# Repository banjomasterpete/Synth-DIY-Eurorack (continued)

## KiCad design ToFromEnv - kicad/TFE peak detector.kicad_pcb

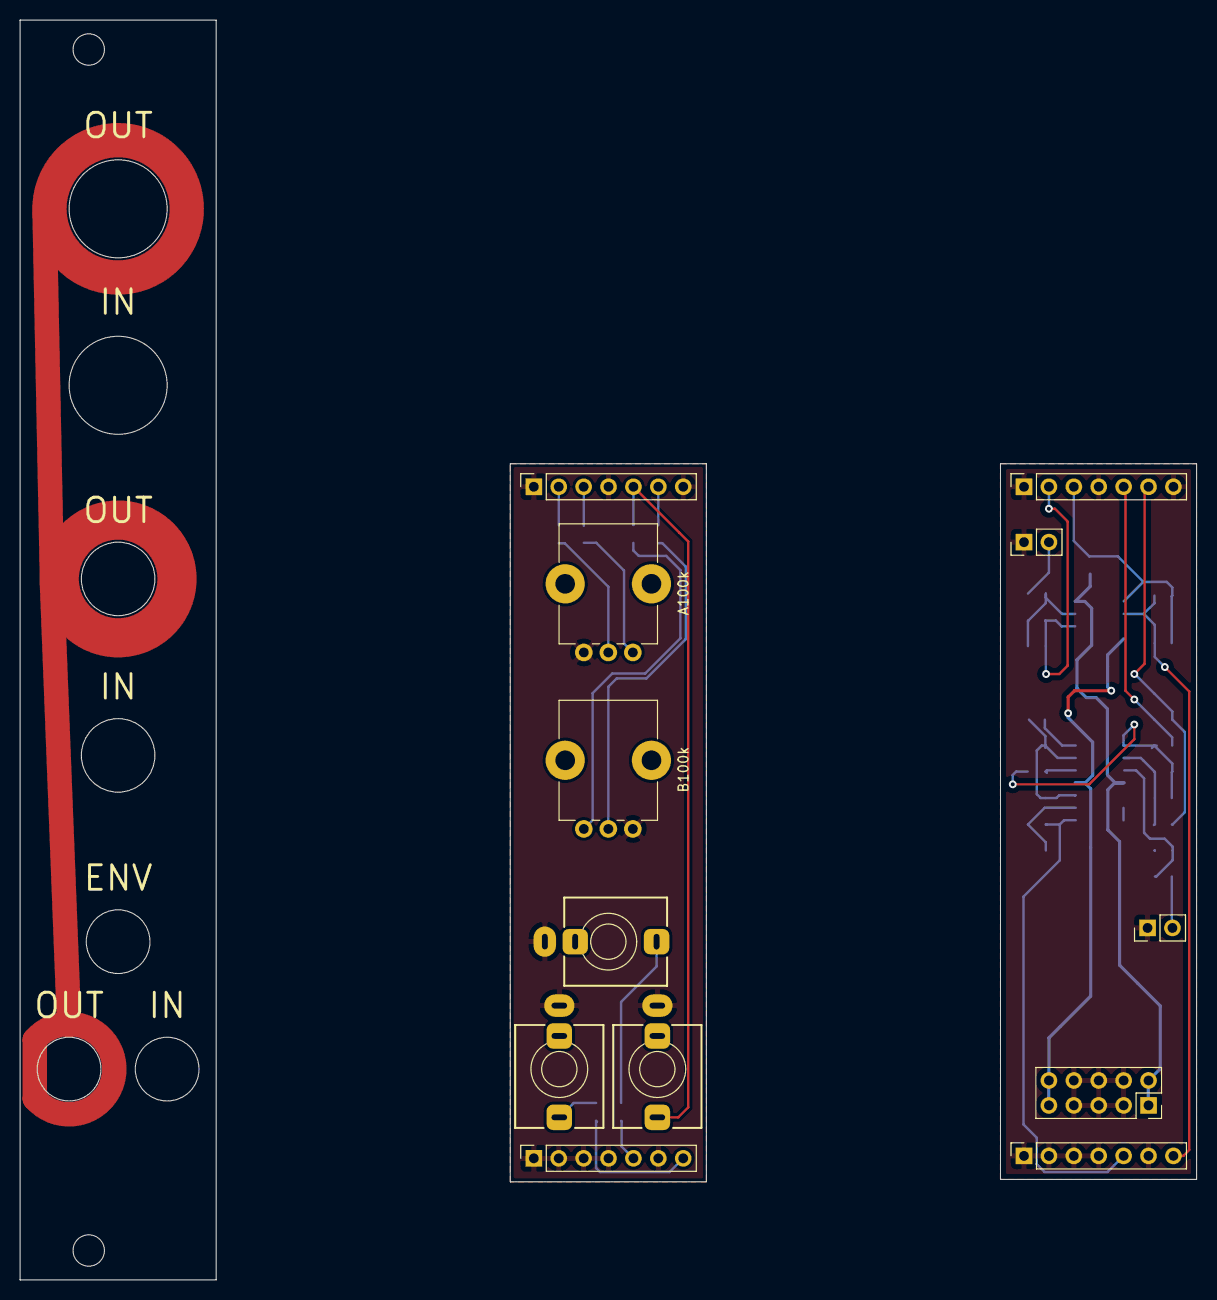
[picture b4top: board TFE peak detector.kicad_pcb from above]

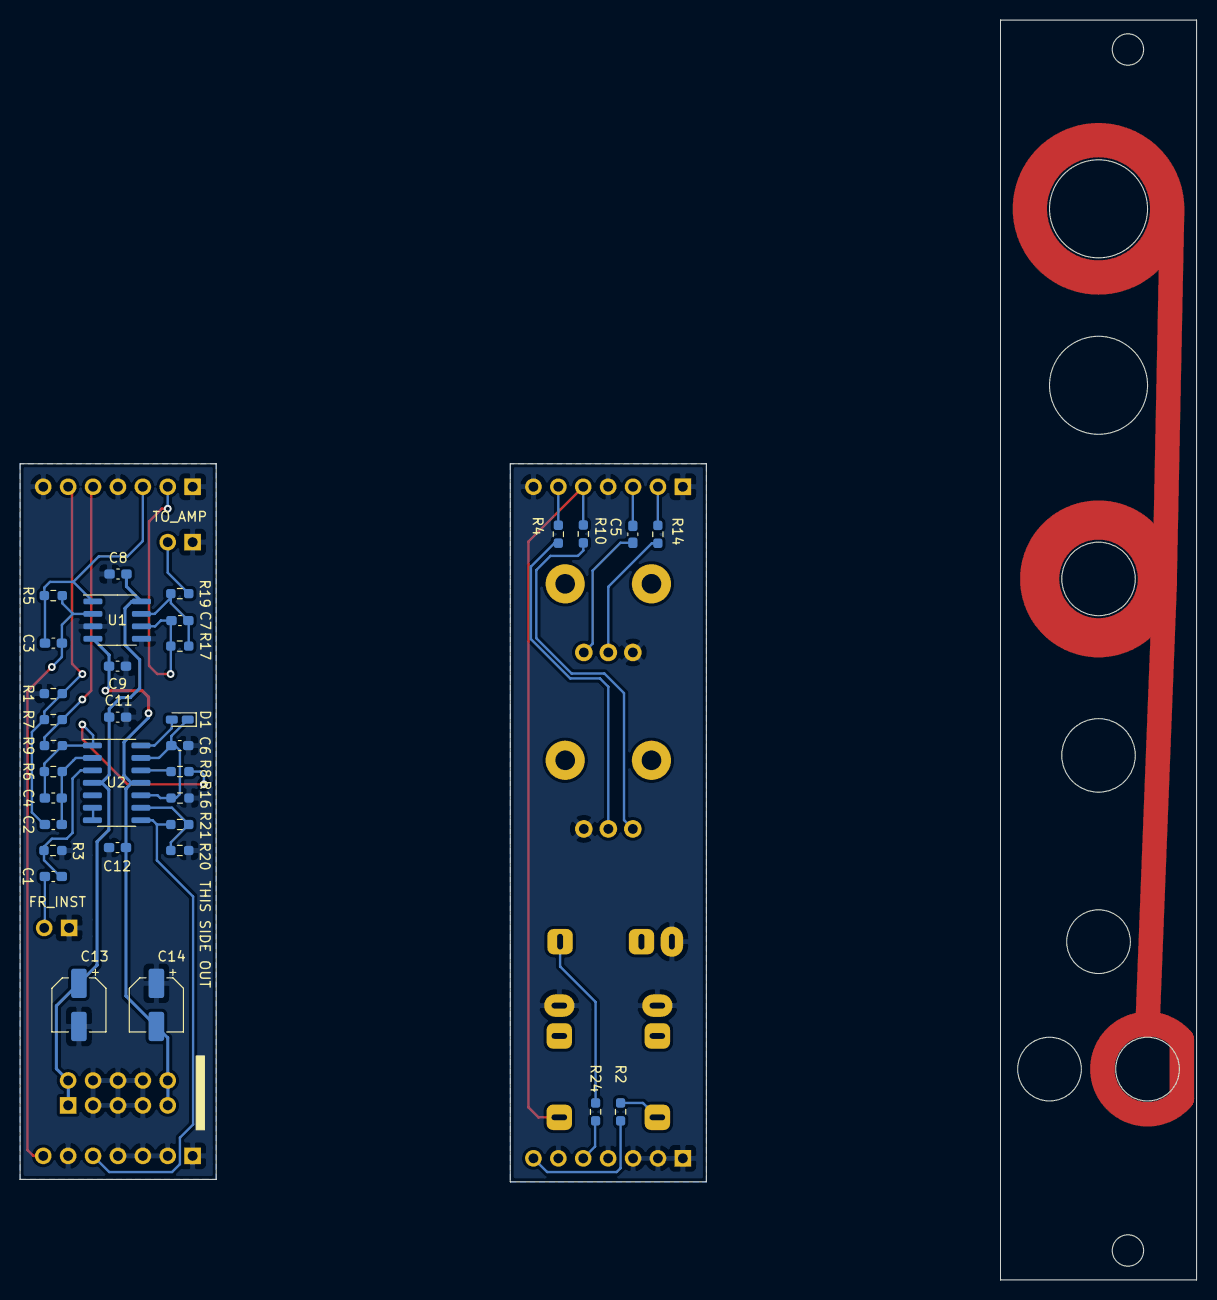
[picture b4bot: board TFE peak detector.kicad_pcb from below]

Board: 2 copper layers, 120.0 x 128.5 mm, 45 parts (33 on the bottom side), 33 nets.

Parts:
C1: 47n; C_0603_1608Metric_Pad1.08x0.95mm_HandSolder
C2: 4.7u; C_0603_1608Metric_Pad1.08x0.95mm_HandSolder
C3, C7: 10p; C_0603_1608Metric_Pad1.08x0.95mm_HandSolder
C4: 100p; C_0603_1608Metric_Pad1.08x0.95mm_HandSolder
C5, C6: 10u; C_0603_1608Metric_Pad1.08x0.95mm_HandSolder
C8, C9, C11, C12: 100n; C_0603_1608Metric_Pad1.08x0.95mm_HandSolder
C13, C14: 10u; CP_Elec_5x5.4
D1: D; D_0603_1608Metric_Castellated
J1: FR_INST; PinHeader_1x02_P2.54mm_Vertical
J2: FR_MOD; Jack_3.5mm_QingPu_WQP-PJ398SM_Vertical
J3: TO_MOD; Jack_3.5mm_QingPu_WQP-PJ398SM_Vertical
J4: TO_AMP; PinHeader_1x02_P2.54mm_Vertical
J5, J9: Conn_01x07_Female; PinSocket_1x07_P2.54mm_Vertical
J6, J10: Conn_01x07_Male; PinSocket_1x07_P2.54mm_Vertical
J7: ENV; Jack_3.5mm_QingPu_WQP-PJ398SM_Vertical
J8: Conn_02x05_Odd_Even; PinSocket_2x05_P2.54mm_Vertical
R1: 6k8; R_0603_1608Metric_Pad0.98x0.95mm_HandSolder
R2: 100k; R_0603_1608Metric_Pad0.98x0.95mm_HandSolder
R3, R6: 2M2; R_0603_1608Metric_Pad0.98x0.95mm_HandSolder
R4: 3k3; R_0603_1608Metric_Pad0.98x0.95mm_HandSolder
R5: 39k; R_0603_1608Metric_Pad0.98x0.95mm_HandSolder
R7: 62k; R_0603_1608Metric_Pad0.98x0.95mm_HandSolder
R8, R19, R24: 1k; R_0603_1608Metric_Pad0.98x0.95mm_HandSolder
R9: 470R; R_0603_1608Metric_Pad0.98x0.95mm_HandSolder
R10: 15k; R_0603_1608Metric_Pad0.98x0.95mm_HandSolder
R14, R16, R17: 10k; R_0603_1608Metric_Pad0.98x0.95mm_HandSolder
R20, R21: 470k; R_0603_1608Metric_Pad0.98x0.95mm_HandSolder
RV1: B100k; Potentiometer_Alps_RK09K_Single_Vertical
RV2: A100k; Potentiometer_Alps_RK09K_Single_Vertical
U1: TL072; SOIC-8_3.9x4.9mm_P1.27mm
U2: TL074; SOIC-14_3.9x8.7mm_P1.27mm

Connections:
+12V: C8.2, C11.2, C13.1, J8.1, J8.2, U1.8, U2.4
-12V: C9.1, C12.1, C14.2, J8.9, J8.10, U1.4, U2.11
ENV_B: J5.5, R21.1, U2.8
ENV_P: J6.5, R24.2
FR_MOD_B: C3.2, J5.7, R5.1, U1.2
FR_MOD_P: J6.7, R2.2
GND: C6.1, C8.1, C9.2, C11.1, C12.2, C13.2, C14.1, J1.1, J4.1, J5.1, J5.2, J5.3, J5.4, J5.6, J8.3, J8.4, J8.5, J8.6, J8.7, J8.8, J9.1, J9.4, J9.7, R1.2, R3.1, R16.2, R20.1, U1.3, U1.5
GND_P: J2.S, J3.S, J6.1, J6.2, J6.3, J6.4, J6.6, J7.S, J10.1, J10.4, J10.7, RV1.1, RV2.3
INST_AMP_2_B: C2.2, J9.6, R1.1, R7.2
INST_AMP_2_P: J10.6, R4.1
INST_AMP_3_B: J9.5, R7.1, R9.2
INST_AMT_3_P: J3.T, J10.5, R10.1
unnamed: C1.1, R3.2, U2.3
unnamed: C1.2, J1.2
unnamed: C2.1, C4.2, R6.1, U2.2
unnamed: C4.1, R6.2, R8.1, R9.1, U2.1
unnamed: C5.2, RV2.1
unnamed: C6.2, D1.1, R16.1, U2.10, U2.13
unnamed: C7.1, R17.2, R19.1, U1.7
unnamed: D1.2, U2.14
unnamed: J2.T, R2.1
unnamed: J4.2, R19.2
unnamed: J7.T, R24.1
unnamed: R4.2, RV1.2
unnamed: R8.2, U2.12
unnamed: R10.2, RV1.3
unnamed: R14.1, RV2.2
unnamed: R20.2, R21.2, U2.9
unnamed: U2.6, U2.7
OUT_AMP_1_B: C3.1, J9.3, R5.2, U1.1
OUT_AMP_1_P: C5.1, J10.3
OUT_AMP_2_B: C7.2, J9.2, R17.1, U1.6
OUT_AMP_2_P: J10.2, R14.2

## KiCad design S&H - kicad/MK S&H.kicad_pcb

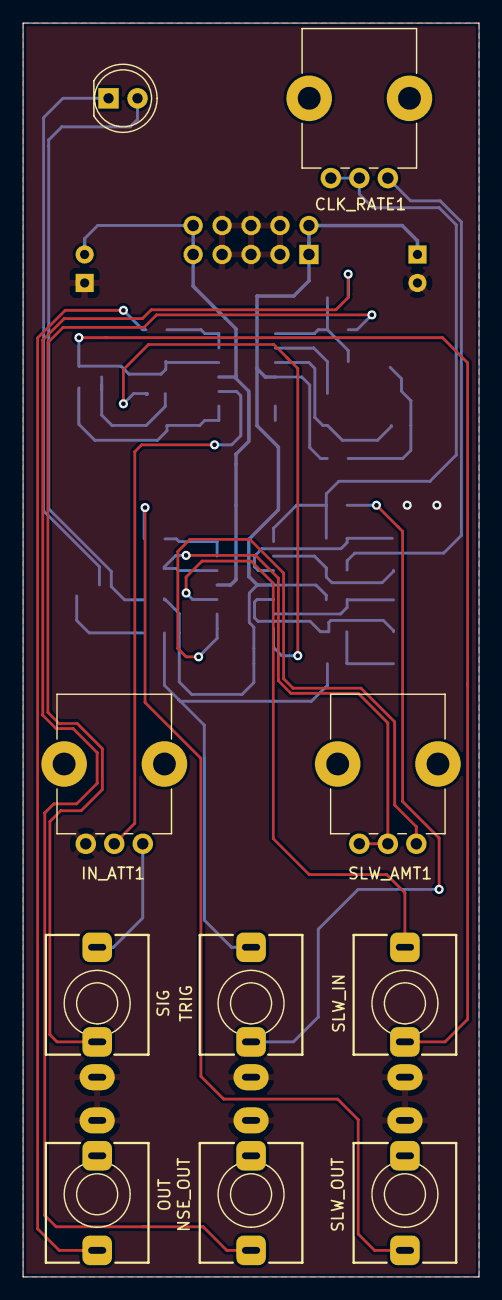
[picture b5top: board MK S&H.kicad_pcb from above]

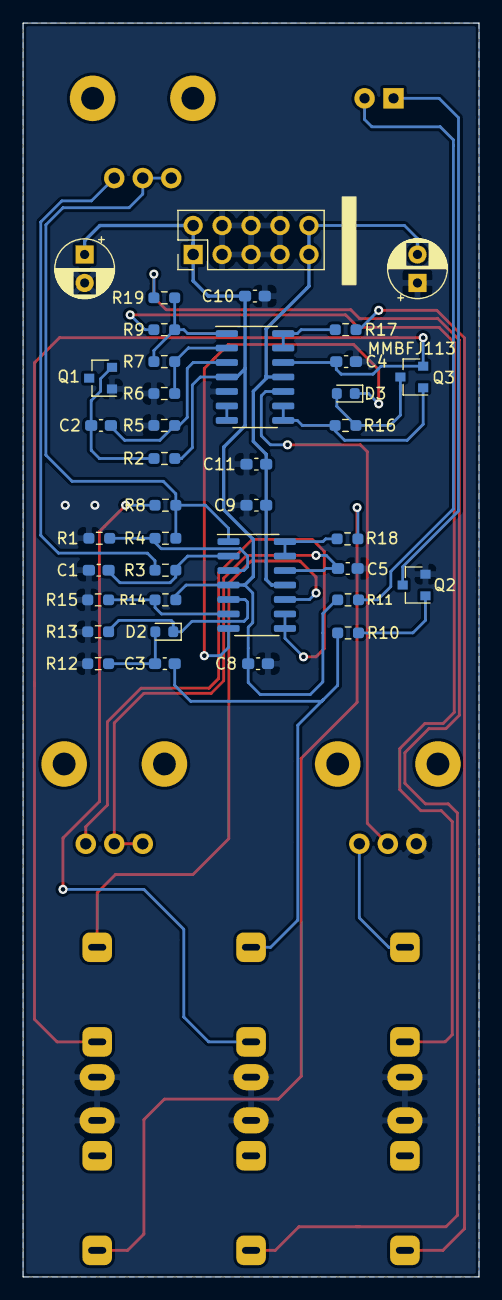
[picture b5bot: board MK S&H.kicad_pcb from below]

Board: 2 copper layers, 40.0 x 110.0 mm, 48 parts (38 on the bottom side), 35 nets.

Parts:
C1, C2: 1uF; C_0603_1608Metric_Pad1.08x0.95mm_HandSolder
C3: 1nF; C_0603_1608Metric_Pad1.08x0.95mm_HandSolder
C4, C8, C9, C10, C11: 100nF; C_0603_1608Metric_Pad1.08x0.95mm_HandSolder
C5: 470nF; C_0603_1608Metric_Pad1.08x0.95mm_HandSolder
C6, C7: CP; CP_Radial_D5.0mm_P2.50mm
CLK_RATE1: 250k; Potentiometer_Alps_RK09K_Single_Vertical
D1: LED; LED_D5.0mm
D2, D3: D; D_0603_1608Metric
IN_ATT1: 100k; Potentiometer_Alps_RK09K_Single_Vertical
J1: TRIG; Jack_3.5mm_QingPu_WQP-PJ398SM_Vertical
J2: SIG; Jack_3.5mm_QingPu_WQP-PJ398SM_Vertical
J3: SLW_IN; Jack_3.5mm_QingPu_WQP-PJ398SM_Vertical
J4: OUT; Jack_3.5mm_QingPu_WQP-PJ398SM_Vertical
J5: SLW_OUT; Jack_3.5mm_QingPu_WQP-PJ398SM_Vertical
J6: Conn_02x05_Odd_Even; PinHeader_2x05_P2.54mm_Vertical
J7: NSE_OUT; Jack_3.5mm_QingPu_WQP-PJ398SM_Vertical
Q1: BC847B; SOT-23
Q2: BC848; SOT-23
Q3: MMBFJ113; SOT-23
R1, R4, R5, R7, R8, R12, R13, R14: 100k; R_0603_1608Metric_Pad0.98x0.95mm_HandSolder
R2: 220k; R_0603_1608Metric_Pad0.98x0.95mm_HandSolder
R3: 2k; R_0603_1608Metric_Pad0.98x0.95mm_HandSolder
R6: 470R; R_0603_1608Metric_Pad0.98x0.95mm_HandSolder
R9, R11, R17, R18, R19: 1k; R_0603_1608Metric_Pad0.98x0.95mm_HandSolder
R10: 51k; R_0603_1608Metric_Pad0.98x0.95mm_HandSolder
R15: 33k; R_0603_1608Metric_Pad0.98x0.95mm_HandSolder
R16: 1M; R_0603_1608Metric_Pad0.98x0.95mm_HandSolder
SLW_AMT1: 100k; Potentiometer_Alps_RK09K_Single_Vertical
U1, U2: TL074; SOIC-14_3.9x8.7mm_P1.27mm

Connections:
+12V: C6.1, C8.1, C10.1, J6.1, J6.2, R2.1, R11.1, R14.2, U1.4, U2.4
-12V: C7.2, C9.2, C11.2, J6.9, J6.10, U1.11, U2.11
GND: C1.2, C4.2, C5.2, C6.2, C7.1, C8.2, C9.1, C10.2, C11.1, IN_ATT1.3, J1.S, J2.S, J3.S, J4.S, J5.S, J6.3, J6.4, J6.5, J6.6, J6.7, J6.8, J7.S, Q1.1, Q2.2, R1.2, R5.2, R6.2, R12.2, R13.2, R15.1, U2.5
NOISE: J2.TN, R9.1
unnamed: C1.1, R3.2, U1.2
unnamed: C2.1, R5.1, U2.3
unnamed: C2.2, Q1.2, R2.2
unnamed: C3.1, D2.2, R12.1
unnamed: C3.2, J1.T, R10.2
unnamed: C4.1, J3.TN, Q3.2, U2.12
unnamed: C5.1, SLW_AMT1.2, SLW_AMT1.3, U1.12
unnamed: CLK_RATE1.1, R3.1
unnamed: CLK_RATE1.2, CLK_RATE1.3, R4.1, R8.2, U1.1
unnamed: D1.1, Q2.3
unnamed: D1.2, R11.2
unnamed: D2.1, R13.1, U1.5
unnamed: D3.1, U1.7
unnamed: D3.2, Q3.3, R16.1
unnamed: IN_ATT1.1, J2.T
unnamed: IN_ATT1.2, U2.10
unnamed: J1.TN, R8.1
unnamed: J3.T, U1.10
unnamed: J4.T, R17.1
unnamed: J5.T, R18.1
unnamed: J7.T, R19.1
unnamed: Q2.1, R10.1
unnamed: Q3.1, R16.2, U2.8, U2.9
unnamed: R1.1, R4.2, U1.3
unnamed: R6.1, R7.1, U2.2
unnamed: R14.1, R15.2, U1.6
unnamed: R17.2, U2.13, U2.14
unnamed: R18.2, U1.13, U1.14
unnamed: R7.2, R9.2, R19.2, U2.1
unnamed: SLW_AMT1.1, U1.8, U1.9
unnamed: U2.6, U2.7

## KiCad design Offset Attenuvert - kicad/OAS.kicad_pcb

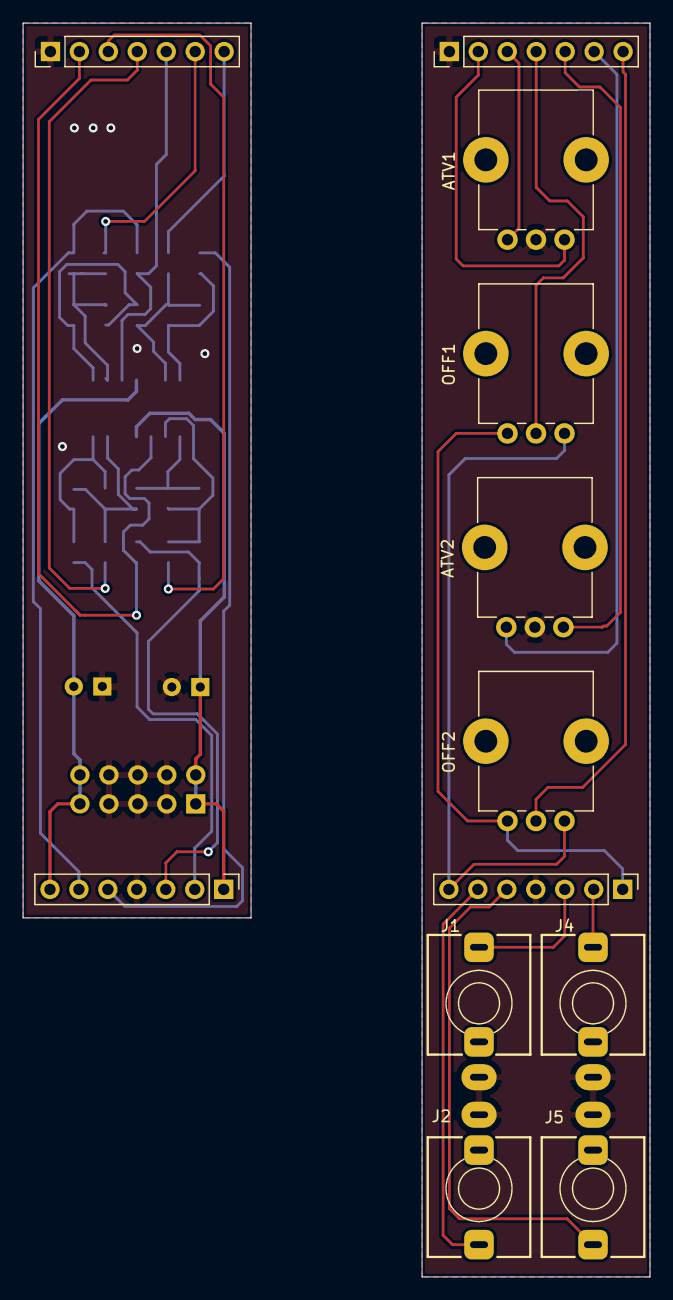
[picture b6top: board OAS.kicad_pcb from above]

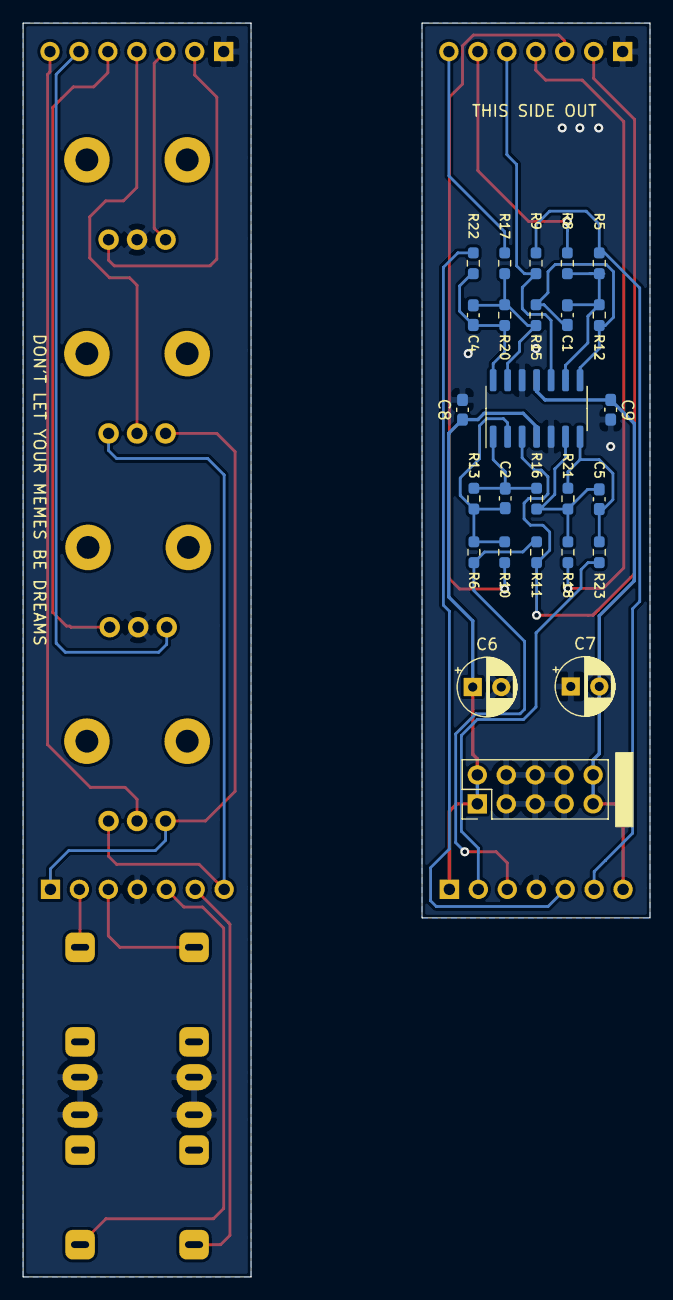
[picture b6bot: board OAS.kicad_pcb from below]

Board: 2 copper layers, 55.0 x 110.0 mm, 38 parts (26 on the bottom side), 34 nets.

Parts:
ATV1, ATV2: 100k; Potentiometer_Alps_RK09K_Single_Vertical
C1, C2, C4, C5: 10pF; C_0603_1608Metric_Pad1.08x0.95mm_HandSolder
C6, C7: 10uF; CP_Radial_D5.0mm_P2.50mm
C8, C9: 100n; C_0603_1608Metric_Pad1.08x0.95mm_HandSolder
J1: IN1; Jack_3.5mm_QingPu_WQP-PJ398SM_Vertical
J2: IN2; Jack_3.5mm_QingPu_WQP-PJ398SM_Vertical
J3, J6: Conn_01x07_Male; PinHeader_1x07_P2.54mm_Vertical
J4: OUT1; Jack_3.5mm_QingPu_WQP-PJ398SM_Vertical
J5: OUT2; Jack_3.5mm_QingPu_WQP-PJ398SM_Vertical
J7: PWR; PinHeader_2x05_P2.54mm_Vertical
J8, J9: Conn_01x07_Female; PinHeader_1x07_P2.54mm_Vertical
OFF1, OFF2: 100k; Potentiometer_Alps_RK09K_Single_Vertical
R5, R6, R9, R11, R12, R13: 100k; R_0603_1608Metric_Pad0.98x0.95mm_HandSolder
R8, R10: 47k; R_0603_1608Metric_Pad0.98x0.95mm_HandSolder
R15, R16, R17, R18, R20, R21: 10k; R_0603_1608Metric_Pad0.98x0.95mm_HandSolder
R22, R23: 1k; R_0603_1608Metric_Pad0.98x0.95mm_HandSolder
U1: TL074; SO-14_3.9x8.65mm_P1.27mm

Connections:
12V_B: C6.1, C8.1, J6.1, J7.1, J7.2, U1.4
12V_P: J9.1, OFF1.3, OFF2.3
-12V_B: C7.2, C9.2, J6.7, J7.9, J7.10, U1.11
-12V_P: J9.7, OFF1.1, OFF2.1
ATV1_1_B: J3.2, R11.2, U1.3
ATV1_1_P: ATV1.1, J8.2
ATV1_3_B: J3.3, R10.2
ATV1_3_P: ATV1.3, J8.3
ATV2_1_B: J3.5, R9.2, U1.10
ATV2_1_P: ATV2.1, J8.5
ATV2_3_B: J3.6, R8.2
ATV2_3_P: ATV2.3, J8.6
GND_B: C6.2, C7.1, C8.2, C9.1, J3.1, J6.4, J7.3, J7.4, J7.5, J7.6, J7.7, J7.8, U1.5, U1.12
GND_P: ATV1.2, ATV2.2, J1.S, J2.S, J4.S, J5.S, J8.1, J9.4
IN1_T_B: J6.3, R6.1, R11.1
IN1_T_P: J1.T, J9.3
IN2_T_B: J6.6, R5.1, R9.1
IN2_T_P: J2.T, J9.6
unnamed: C1.1, R12.2, R15.1, U1.8
unnamed: C1.2, R5.2, R8.1, R12.1, U1.9
unnamed: C2.1, R13.2, R16.1, U1.1
unnamed: C2.2, R6.2, R10.1, R13.1, U1.2
unnamed: C4.1, R20.2, R22.1, U1.14
unnamed: C4.2, R15.2, R17.2, R20.1, U1.13
unnamed: C5.1, R21.2, R23.1, U1.7
unnamed: C5.2, R16.2, R18.2, R21.1, U1.6
OFF1_2_B: J3.4, R18.1
OFF1_2_P: J8.4, OFF1.2
OFF2_2_B: J3.7, R17.1
OFF2_2_P: J8.7, OFF2.2
OUT1_T_B: J6.2, R23.2
OUT1_T_P: J4.T, J9.2
OUT2_T_B: J6.5, R22.2
OUT2_T_P: J5.T, J9.5

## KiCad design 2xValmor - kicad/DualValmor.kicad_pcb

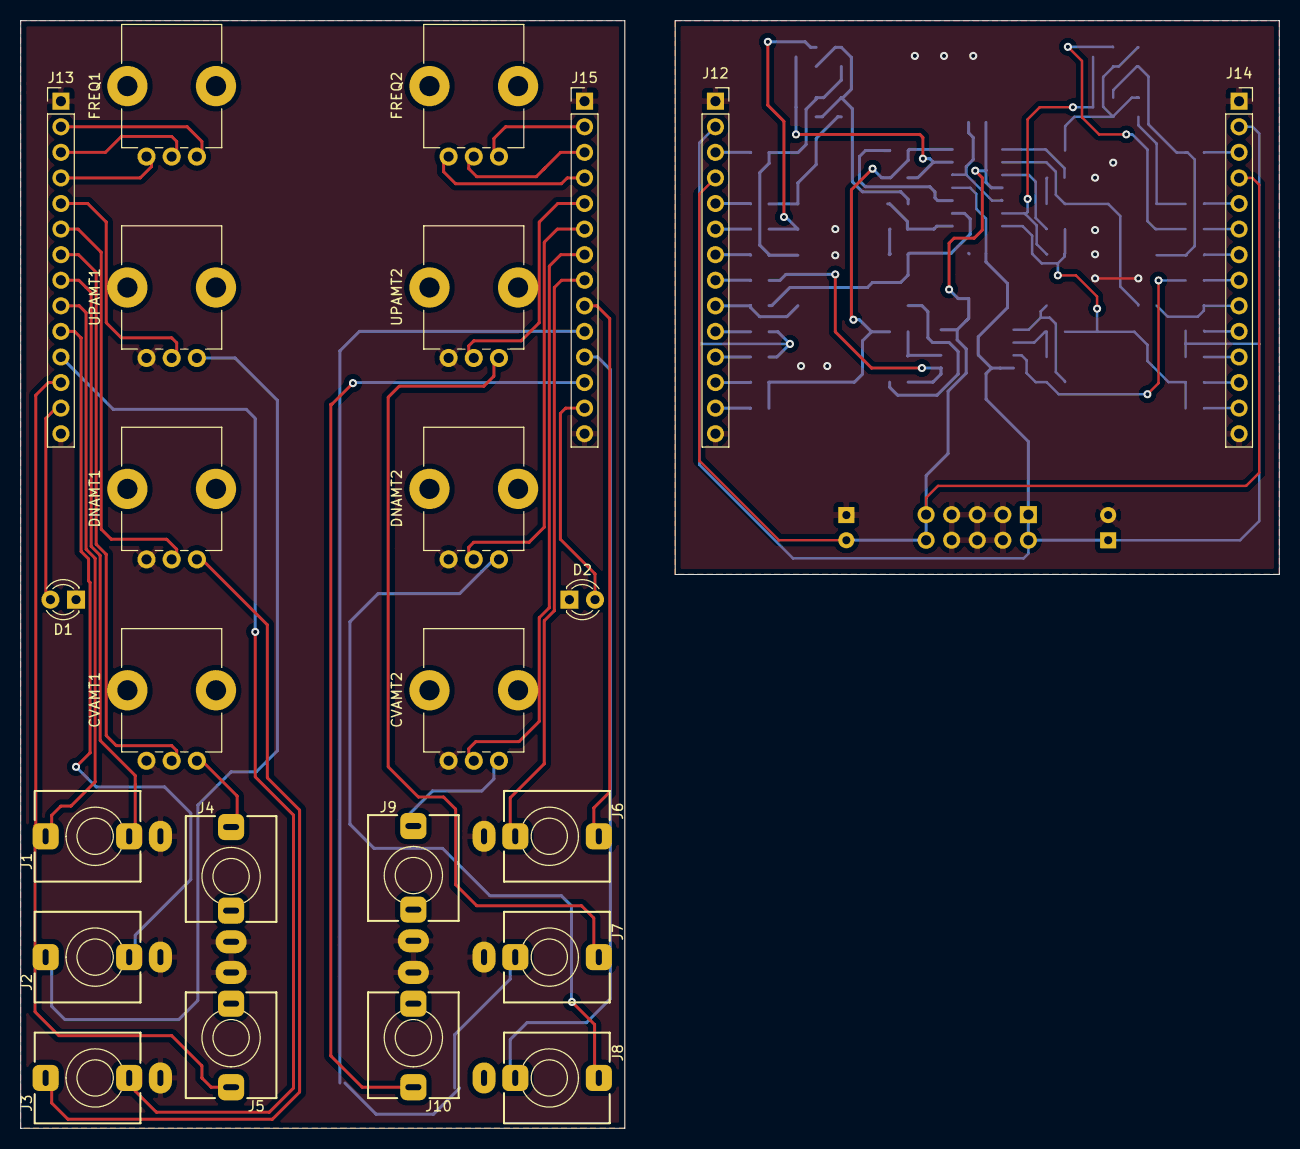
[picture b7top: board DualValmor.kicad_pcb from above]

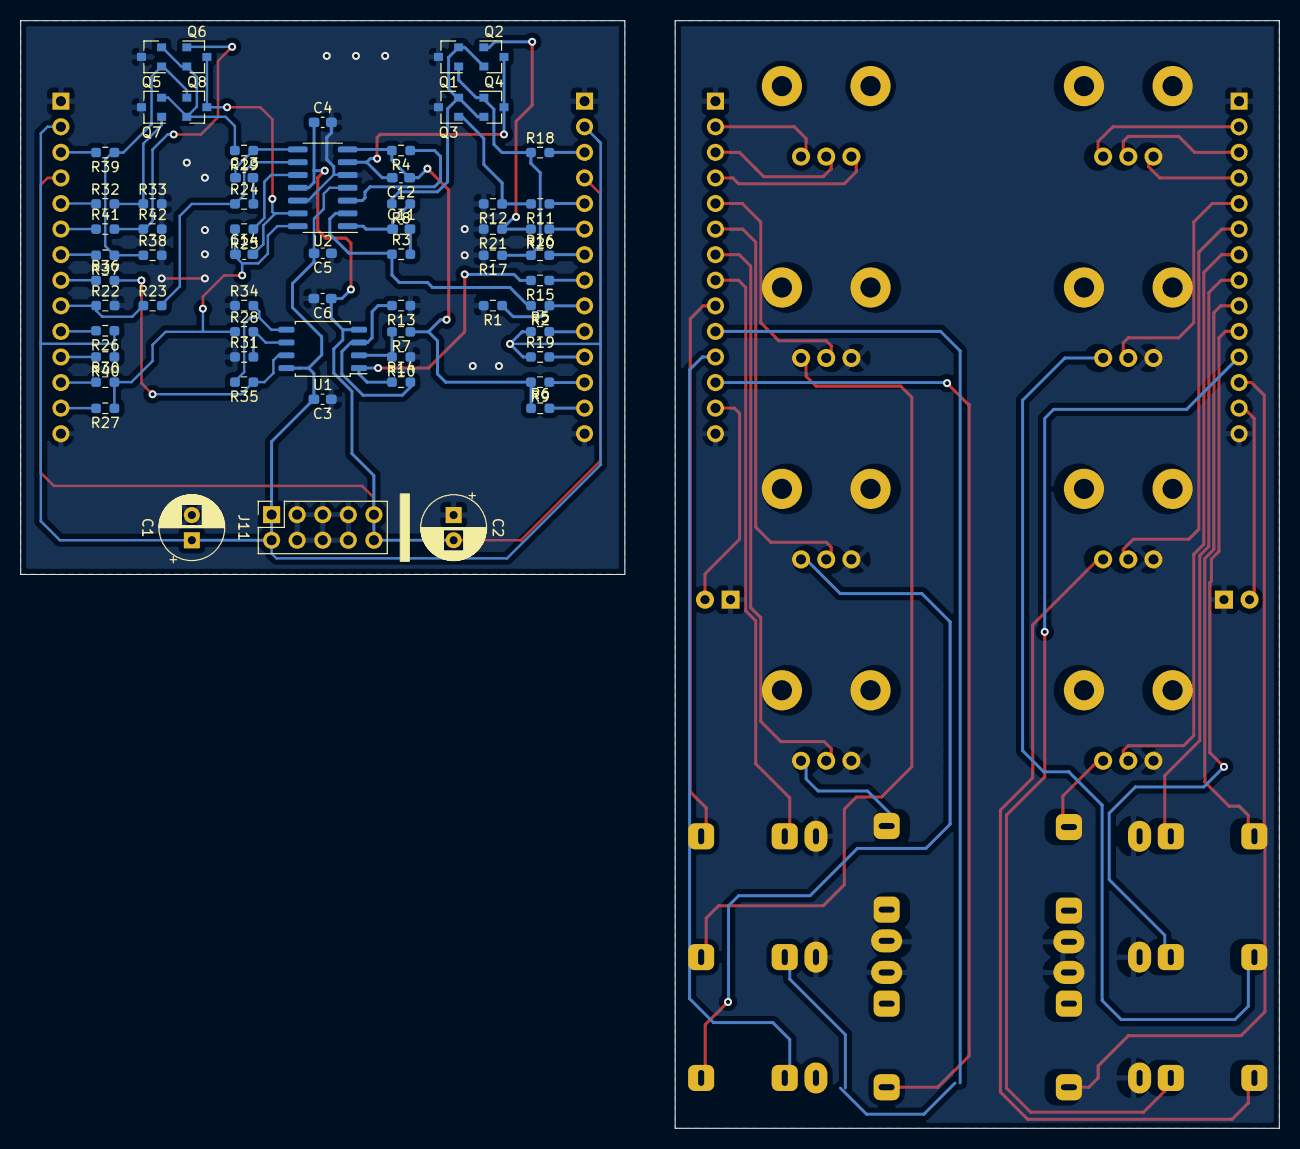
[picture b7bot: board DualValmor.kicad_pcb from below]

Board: 2 copper layers, 125.0 x 110.0 mm, 87 parts (63 on the bottom side), 79 nets.

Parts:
C1, C2: 10u; CP_Radial_D6.3mm_P2.50mm
C3, C4, C5, C6: 100n; C_0603_1608Metric_Pad1.08x0.95mm_HandSolder
C11, C13: 22p; C_0603_1608Metric_Pad1.08x0.95mm_HandSolder
C12, C14: 22n; C_0603_1608Metric_Pad1.08x0.95mm_HandSolder
CVAMT1, CVAMT2: 100k; Potentiometer_Bourns_PTV09A-1_Single_Vertical
D1, D2: LED; LED_D3.0mm
DNAMT1, DNAMT2: 100k; Potentiometer_Bourns_PTV09A-1_Single_Vertical
FREQ1, FREQ2: 100k; Potentiometer_Bourns_PTV09A-1_Single_Vertical
J1: GATE1; Jack_3.5mm_QingPu_WQP-PJ398SM_Vertical
J2: UP1; Jack_3.5mm_QingPu_WQP-PJ398SM_Vertical
J3: DOWN1; Jack_3.5mm_QingPu_WQP-PJ398SM_Vertical
J4: FREQ_CV1; Jack_3.5mm_QingPu_WQP-PJ398SM_Vertical
J5: OUT1; Jack_3.5mm_QingPu_WQP-PJ398SM_Vertical
J6: GATE2; Jack_3.5mm_QingPu_WQP-PJ398SM_Vertical
J7: UP2; Jack_3.5mm_QingPu_WQP-PJ398SM_Vertical
J8: DOWN2; Jack_3.5mm_QingPu_WQP-PJ398SM_Vertical
J9: FREQ_CV2; Jack_3.5mm_QingPu_WQP-PJ398SM_Vertical
J10: OUT2; Jack_3.5mm_QingPu_WQP-PJ398SM_Vertical
J11: Conn_02x05_Odd_Even; PinSocket_2x05_P2.54mm_Vertical
J12, J14: Conn_01x14_Female; PinSocket_1x14_P2.54mm_Vertical
J13, J15: Conn_01x14_Male; PinHeader_1x14_P2.54mm_Vertical
Q1, Q2, Q5, Q6: BC857; SOT-23
Q3, Q4, Q7, Q8: BC847; SOT-23
R1, R2, R7, R10, R11, R13, R16, R18, R20, R22, R23, R28, R31, R32, R34, R37, R39, R41: 100k; R_0603_1608Metric_Pad0.98x0.95mm_HandSolder
R3, R24: 10M; R_0603_1608Metric_Pad0.98x0.95mm_HandSolder
R4, R14, R25, R35: 220k; R_0603_1608Metric_Pad0.98x0.95mm_HandSolder
R5, R8, R19, R26, R29, R40: 10k; R_0603_1608Metric_Pad0.98x0.95mm_HandSolder
R6, R12, R21, R27, R33, R42: 3k3; R_0603_1608Metric_Pad0.98x0.95mm_HandSolder
R9, R15, R30, R36: 1k; R_0603_1608Metric_Pad0.98x0.95mm_HandSolder
R17, R38: 1k8; R_0603_1608Metric_Pad0.98x0.95mm_HandSolder
U1: TL072; SOIC-8_5.23x5.23mm_P1.27mm
U2: TL074; SOIC-14_3.9x8.7mm_P1.27mm
UPAMT1, UPAMT2: 100k; Potentiometer_Bourns_PTV09A-1_Single_Vertical

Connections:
+12V: C1.1, C3.2, C5.2, J11.1, J11.2, J12.2, J14.2, R5.1, R19.1, R26.1, R40.1, U1.8, U2.4
-12V: C2.2, C4.1, C6.1, J11.9, J11.10, J12.4, J14.4, U1.4, U2.11
/CVAMT1_WIPER_B: J12.7, R16.2
/CVAMT1_WIPER_PA: CVAMT1.2, J13.7
/CVAMT2_WIPER_B: J14.7, R37.2
/CVAMT2_WIPER_PA: CVAMT2.2, J15.7
/DNAMT1_WIPER_B: J12.6, R20.1
/DNAMT1_WIPER_PA: DNAMT1.2, J13.6
/DNAMT2_WIPER_B: J14.6, R41.1
/DNAMT2_WIPER_PA: DNAMT2.2, J15.6
/DOWN1_TN_B: J12.11, R19.2
/DOWN1_TN_PA: J3.TN, J13.11
/DOWN2_TN_B: J14.11, R40.2
/DOWN2_TN_PA: J8.TN, J15.11
/FREQ1_P1_PA: FREQ1.1, J13.2
/FREQ1_P3_PA: FREQ1.3, J13.4
/FREQ1_WIPER_B: J12.3, R18.2
/FREQ1_WIPER_PA: FREQ1.2, J13.3
/FREQ2_P1_PA: FREQ2.1, J15.2
/FREQ2_P3_PA: FREQ2.3, J15.4
/FREQ2_WIPER_B: J14.3, R39.2
/FREQ2_WIPER_PA: FREQ2.2, J15.3
/GATE1_TN_B: J12.8, R15.1
/GATE1_TN_PA: J1.TN, J13.8
/GATE1_T_B: J12.9, R1.1, R2.1
/GATE1_T_PA: J1.T, J13.9
/GATE2_TN_B: J14.8, R36.1
/GATE2_TN_PA: J6.TN, J15.8
/GATE2_T_B: J14.9, R22.1, R23.1
/GATE2_T_PA: J6.T, J15.9
/LED1_B: J12.13, R6.2
/LED1_PA: D1.2, J13.13
/LED2_B: J14.13, R27.2
/LED2_PA: D2.2, J15.13
/OUT1_T_B: J12.12, R9.1
/OUT1_T_PA: J5.T, J13.12
/OUT2_T_B: J14.12, R30.1
/OUT2_T_PA: J10.T, J15.12
/UP1_TN_B: J12.10, R5.2
/UP1_TN_PA: J2.TN, J13.10
/UP2_TN_B: J14.10, R26.2
/UP2_TN_PA: J7.TN, J15.10
/UPAMT1_WIPER_B: J12.5, R11.1
/UPAMT1_WIPER_PA: J13.5, UPAMT1.2
/UPAMT2_WIPER_B: J14.5, R32.1
/UPAMT2_WIPER_PA: J15.5, UPAMT2.2
GND: C1.2, C2.1, C3.1, C4.2, C5.1, C6.2, CVAMT1.3, CVAMT2.3, D1.1, D2.1, DNAMT1.3, DNAMT2.3, J1.S, J2.S, J3.S, J4.S, J5.S, J6.S, J7.S, J9.S, J10.S, J11.3, J11.4, J11.5, J11.6, J11.7, J11.8, J12.1, J12.14, J13.1, J13.14, J14.1, J14.14, J15.1, J15.14, Q1.3, Q3.3, Q5.3, Q7.3, R1.2, R10.1, R12.2, R13.1, R17.2, R21.2, R22.2, R31.1, R33.2, R34.1, R38.2, R42.2, U2.5, U2.12, UPAMT1.3, UPAMT2.3
unnamed: C11.1, R8.1, U2.1
unnamed: C11.2, R3.2
unnamed: C12.1, R4.2, R6.1, R7.1, R9.2, U2.7
unnamed: C12.2, Q2.3, Q4.3, U2.6
unnamed: C13.1, R29.1, U2.8
unnamed: C13.2, R24.2
unnamed: C14.1, R25.2, R27.1, R28.1, R30.2, U2.14
unnamed: C14.2, Q6.3, Q8.3, U2.13
unnamed: CVAMT1.1, J4.T
unnamed: CVAMT2.1, J9.T
unnamed: DNAMT1.1, J3.T
unnamed: DNAMT2.1, J8.T
unnamed: J2.T, UPAMT1.1
unnamed: J7.T, UPAMT2.1
unnamed: Q1.1, Q4.1, R16.1, R17.1, R18.1
unnamed: Q1.2, Q2.2, Q3.2, Q4.2, R8.2
unnamed: Q2.1, R20.2, R21.1
unnamed: Q3.1, R11.2, R12.1
unnamed: Q5.1, Q8.1, R37.1, R38.1, R39.1
unnamed: Q5.2, Q6.2, Q7.2, Q8.2, R29.2
unnamed: Q6.1, R41.2, R42.1
unnamed: Q7.1, R32.2, R33.1
unnamed: R2.2, R3.1, U2.2
unnamed: R4.1, U2.3
unnamed: R7.2, R10.2, U1.2
unnamed: R13.2, R14.2, U1.3
unnamed: R14.1, R15.2, U1.1
unnamed: R23.2, R24.1, U2.9
unnamed: R25.1, U2.10
unnamed: R28.2, R31.2, U1.6
unnamed: R34.2, R35.2, U1.5
unnamed: R35.1, R36.2, U1.7

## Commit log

2021-04-17 Create YuFolder Docs
2021-12-09 Add files via upload
    This knob should fit pretty much any shaft type. The side hole is sized for #4-40 heat set inserts from McMaster Carr
    Inserts PN: 93365A120
    Set screws PN: 94355A130
2023-09-10 6HP Precision Mult & Adder
    This is a multiple/ adder utility that is precise enough to use for v/oct signals.
    2x 1 to 3 buffered mults (channel 2 normals to 1)
    2x 3 to 1 buffered adders
2023-09-15 Add files via upload
    Added schematic pdf
2024-02-21 Create DPG (voltage-controlled distortion) - kicad
2024-02-21 Create VCD
